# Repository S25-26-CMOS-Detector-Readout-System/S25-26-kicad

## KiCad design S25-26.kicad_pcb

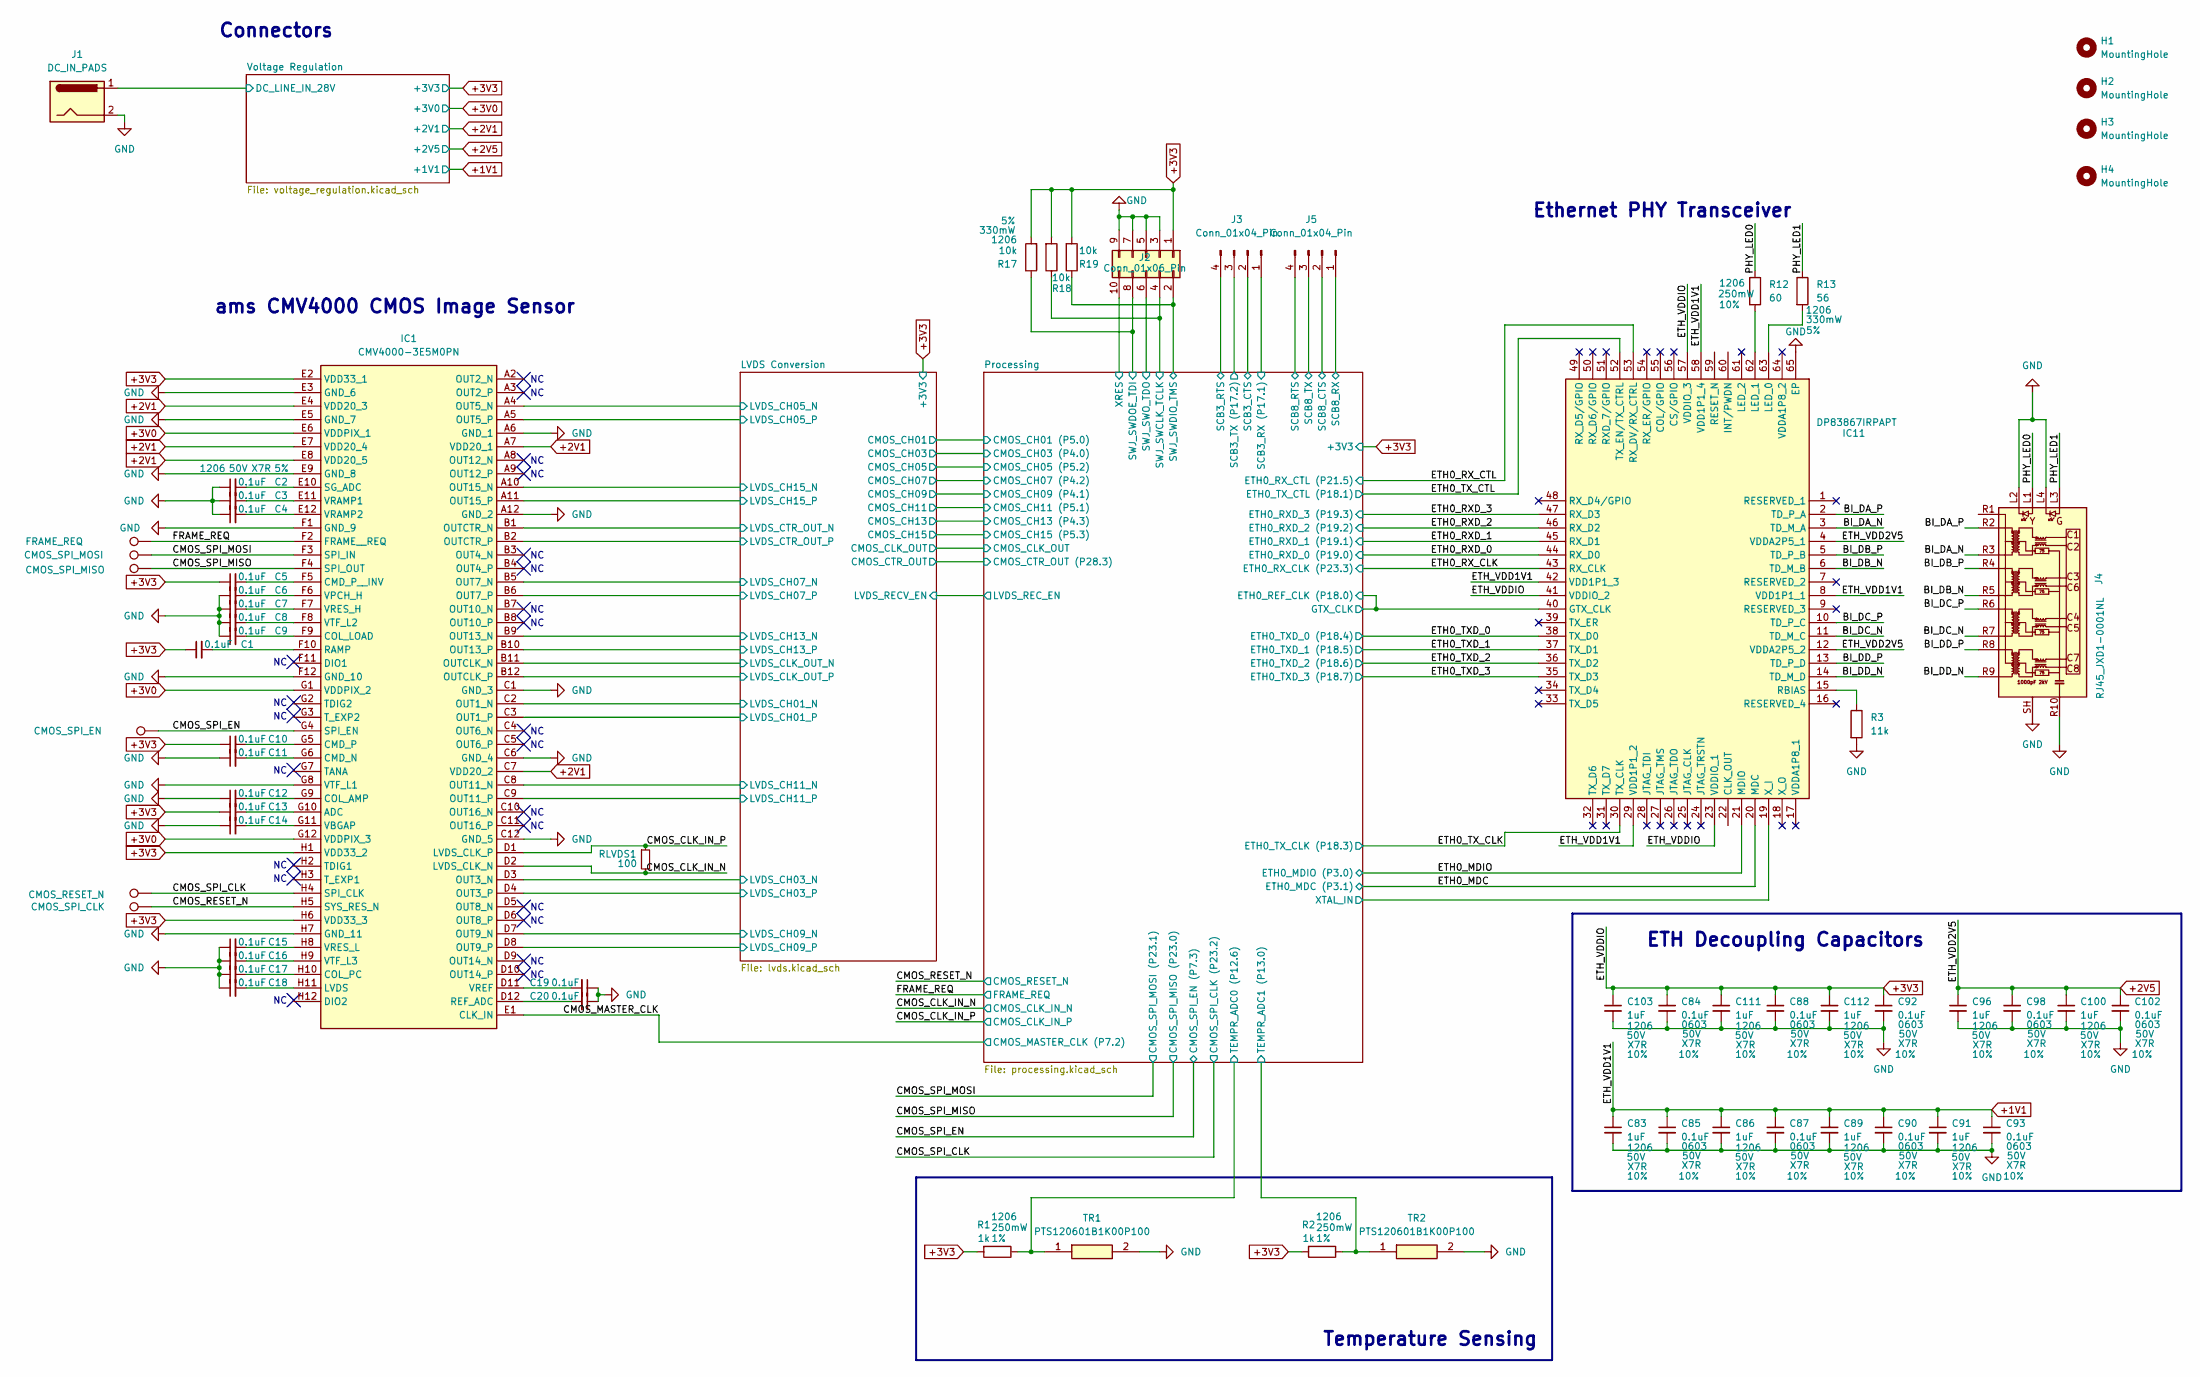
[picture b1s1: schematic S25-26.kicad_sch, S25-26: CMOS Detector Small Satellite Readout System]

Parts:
C1, C2, C3, C4, C5, C6, C7, C8, C9, C10, C11, C12, C13, C14, C15, C16, C17, C18, C19, C20: 0.1uF; C_1206_3216Metric; Voltage Rating 50V; Tolerance 5%; Mouser Part Number 581-12065C104J4Z2A
C83, C86, C89, C91, C96, C100, C103, C111, C112: 1uF; C_1206_3216Metric; Voltage Rating 50V; Tolerance 10%; Mouser Part Number 963-UMK316B7105KL-T
C84, C85, C87, C88, C90, C92, C93, C98, C102: 0.1uF; C_0603_1608Metric; Voltage Rating 50V; Tolerance 10%; Mouser Part Number 963-UMK107B7104KAHT
CMOS_RESET_N1: CMOS_RESET_N; TestPoint_Pad_2.0x2.0mm
CMOS_SCLK1: CMOS_SPI_CLK; TestPoint_Pad_2.0x2.0mm
CMOS_SPI_EN1: CMOS_SPI_EN; TestPoint_Pad_2.0x2.0mm
CMOS_SPI_MISO1: CMOS_SPI_MISO; TestPoint_Pad_2.0x2.0mm
CMOS_SPI_MOSI1: CMOS_SPI_MOSI; TestPoint_Pad_2.0x2.0mm
FRAME_REQ1: FRAME_REQ; TestPoint_Pad_2.0x2.0mm
H1, H2, H3, H4: MountingHole; MountingHole_2.7mm_Keepout
IC1: CMV4000-3E5M0PN; CMV40003E5M0PN_Socket; Manufacturer_Part_Number CMV4000-3E5M0PN
IC11: DP83867IRPAPT; QFP50P1200X1200X120-65N; Mouser Part Number 595-DP83867IRPAPT
J1: DC_IN_PADS; SolderWire-2sqmm_1x02_P7.8mm_D2mm_OD3.9mm
J2: Conn_01x06_Pin; PinHeader_2x05_P1.27mm_Vertical_SMD
J3, J5: Conn_01x04_Pin; PinHeader_1x04_P2.54mm_Vertical
J4: RJ45_JXD1-0001NL; Digikey Part Number 553-3266-ND
R1, R2: 1k; R_1206_3216Metric; Power Rating 250mW; Tolerance 1%; Mouser Part Number 71-RCA12061K00FKEA
R3: 11k; R_1206_3216Metric
R12: 60; R_1206_3216Metric; Power Rating 250mW; Tolerance 10%; Mouser Part Number 71-CRCW120660R0KNAIF
R13: 56; R_1206_3216Metric; Power Rating 330mW; Tolerance 5%; Mouser Part Number 667-ERJ-T08J560V
R17, R18, R19: 10k; R_1206_3216Metric; Power Rating 330mW; Tolerance 5%; Mouser Part Number 667-ERJ-T08J103V
RLVDS1: 100; R_0603_1608Metric; Power Rating 0.2W; Tolerance 1%; Mouser Part Number 667-ERJ-P03F1000V
TR1, TR2: PTS120601B1K00P100; RESC3016X65N; Manufacturer_Part_Number PTS120601B1K00P100; Mouser Part Number 594-PTS120601B1K00P

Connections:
+1V1: C83.1, C85.1, C86.1, C87.1, C89.1, C90.1, C91.1, C93.1, IC11.8 (VDD1P1_1), IC11.29 (VDD1P1_2), IC11.42 (VDD1P1_3), IC11.58 (VDD1P1_4); also elsewhere on the board
+2V1: IC1.A7 (VDD20_1), IC1.C7 (VDD20_2), IC1.E4 (VDD20_3), IC1.E7 (VDD20_4), IC1.E8 (VDD20_5); also elsewhere on the board
+2V5: C96.1, C98.1, C100.1, C102.1, IC11.4 (VDDA2P5_1), IC11.12 (VDDA2P5_2); also elsewhere on the board
+3V0: IC1.E6 (VDDPIX_1), IC1.G1 (VDDPIX_2), IC1.G12 (VDDPIX_3); also elsewhere on the board
+3V3: C1.1, C5.1, C10.1, C13.1, C84.1, C88.1, C92.1, C103.1, C111.1, C112.1, IC1.E2 (VDD33_1), IC1.H1 (VDD33_2), IC1.H6 (VDD33_3), IC11.23 (VDDIO_1), IC11.41 (VDDIO_2), IC11.57 (VDDIO_3), J2.1, R1.2, R2.2, R17.2, R18.2, R19.2; also elsewhere on the board
/BI_DA_N: IC11.3 (TD_M_A), J4.R3 (TD1-)
/BI_DA_P: IC11.2 (TD_P_A), J4.R2 (TD1+)
/BI_DB_N: IC11.6 (TD_M_B), J4.R5 (TD2-)
/BI_DB_P: IC11.5 (TD_P_B), J4.R4 (TD2+)
/BI_DC_N: IC11.11 (TD_M_C), J4.R7 (TD3-)
/BI_DC_P: IC11.10 (TD_P_C), J4.R6 (TD3+)
/BI_DD_N: IC11.14 (TD_M_D), J4.R9 (TD4-)
/BI_DD_P: IC11.13 (TD_P_D), J4.R8 (TD4+)
/CMOS_CLK_IN_N: IC1.D2 (LVDS_CLK_N), RLVDS1.2; also elsewhere on the board
/CMOS_CLK_IN_P: IC1.D1 (LVDS_CLK_P), RLVDS1.1; also elsewhere on the board
/CMOS_MASTER_CLK: IC1.E1 (CLK_IN); also elsewhere on the board
/CMOS_RESET_N: CMOS_SCLK1.1, IC1.H5 (SYS_RES_N); also elsewhere on the board
/CMOS_SPI_CLK: CMOS_RESET_N1.1, IC1.H4 (SPI_CLK); also elsewhere on the board
/CMOS_SPI_EN: CMOS_SPI_EN1.1, IC1.G4 (SPI_EN); also elsewhere on the board
/CMOS_SPI_MISO: CMOS_SPI_MISO1.1, IC1.F4 (SPI_OUT); also elsewhere on the board
/CMOS_SPI_MOSI: CMOS_SPI_MOSI1.1, IC1.F3 (SPI_IN); also elsewhere on the board
/ETH0_MDC: IC11.20 (MDC); also elsewhere on the board
/ETH0_MDIO: IC11.21 (MDIO); also elsewhere on the board
/ETH0_RXD_0: IC11.44 (RX_D0); also elsewhere on the board
/ETH0_RXD_1: IC11.45 (RX_D1); also elsewhere on the board
/ETH0_RXD_2: IC11.46 (RX_D2); also elsewhere on the board
/ETH0_RXD_3: IC11.47 (RX_D3); also elsewhere on the board
/ETH0_RX_CLK: IC11.43 (RX_CLK); also elsewhere on the board
/ETH0_RX_CTL: IC11.53 (RX_DV/RX_CTRL); also elsewhere on the board
/ETH0_TXD_0: IC11.38 (TX_D0); also elsewhere on the board
/ETH0_TXD_1: IC11.37 (TX_D1); also elsewhere on the board
/ETH0_TXD_2: IC11.36 (TX_D2); also elsewhere on the board
/ETH0_TXD_3: IC11.35 (TX_D3); also elsewhere on the board
/ETH0_TX_CLK: IC11.30 (TX_CLK); also elsewhere on the board
/ETH0_TX_CTL: IC11.52 (TX_EN/TX_CTRL); also elsewhere on the board
/FRAME_REQ: FRAME_REQ1.1, IC1.F2 (FRAME__REQ); also elsewhere on the board
/LVDS Conversion/LVDS_CH01_N: IC1.C2 (OUT1_N); also elsewhere on the board
/LVDS Conversion/LVDS_CH01_P: IC1.C3 (OUT1_P); also elsewhere on the board
/LVDS Conversion/LVDS_CH03_N: IC1.D3 (OUT3_N); also elsewhere on the board
/LVDS Conversion/LVDS_CH03_P: IC1.D4 (OUT3_P); also elsewhere on the board
/LVDS Conversion/LVDS_CH05_N: IC1.A4 (OUT5_N); also elsewhere on the board
/LVDS Conversion/LVDS_CH05_P: IC1.A5 (OUT5_P); also elsewhere on the board
/LVDS Conversion/LVDS_CH07_N: IC1.B5 (OUT7_N); also elsewhere on the board
/LVDS Conversion/LVDS_CH07_P: IC1.B6 (OUT7_P); also elsewhere on the board
/LVDS Conversion/LVDS_CH09_N: IC1.D7 (OUT9_N); also elsewhere on the board
/LVDS Conversion/LVDS_CH09_P: IC1.D8 (OUT9_P); also elsewhere on the board
/LVDS Conversion/LVDS_CH11_N: IC1.C8 (OUT11_N); also elsewhere on the board
/LVDS Conversion/LVDS_CH11_P: IC1.C9 (OUT11_P); also elsewhere on the board
/LVDS Conversion/LVDS_CH13_N: IC1.B9 (OUT13_N); also elsewhere on the board
/LVDS Conversion/LVDS_CH13_P: IC1.B10 (OUT13_P); also elsewhere on the board
/LVDS Conversion/LVDS_CH15_N: IC1.A10 (OUT15_N); also elsewhere on the board
/LVDS Conversion/LVDS_CH15_P: IC1.A11 (OUT15_P); also elsewhere on the board
/LVDS Conversion/LVDS_CLK_OUT_N: IC1.B11 (OUTCLK_N); also elsewhere on the board
/LVDS Conversion/LVDS_CLK_OUT_P: IC1.B12 (OUTCLK_P); also elsewhere on the board
/LVDS Conversion/LVDS_CTR_OUT_N: IC1.B1 (OUTCTR_N); also elsewhere on the board
/LVDS Conversion/LVDS_CTR_OUT_P: IC1.B2 (OUTCTR_P); also elsewhere on the board
/PHY_LED0: J4.L1, R12.1
/PHY_LED1: J4.L3, R13.1
/Processing/ETH0_REF_CLK (P18.0): IC11.40 (GTX_CLK); also elsewhere on the board
/Processing/SCB3_CTS: J3.2; also elsewhere on the board
/Processing/SCB3_RTS: J3.4; also elsewhere on the board
/Processing/SCB3_RX (P17.1): J3.1; also elsewhere on the board
/Processing/SCB3_TX (P17.2): J3.3; also elsewhere on the board
/Processing/SCB8_CTS: J5.2; also elsewhere on the board
/Processing/SCB8_RTS: J5.4; also elsewhere on the board
/Processing/SCB8_RX: J5.1; also elsewhere on the board
/Processing/SCB8_TX: J5.3; also elsewhere on the board
/Processing/SWJ_SWCLK_TCLK: J2.4, R18.1; also elsewhere on the board
/Processing/SWJ_SWDIO_TMS: J2.2, R19.1; also elsewhere on the board
/Processing/SWJ_SWDOE_TDI: J2.8, R17.1; also elsewhere on the board
/Processing/SWJ_SWO_TDO: J2.6; also elsewhere on the board
/Processing/TEMPR_ADC0 (P12.6): R1.1, TR1.1; also elsewhere on the board
/Processing/TEMPR_ADC1 (P13.0): R2.1, TR2.1; also elsewhere on the board
/Processing/XRES: J2.10; also elsewhere on the board
/Processing/XTAL_IN: IC11.19 (X_I); also elsewhere on the board
/Voltage Regulation/DC_LINE_IN_28V: J1.1; also elsewhere on the board
GND: C2.1, C3.1, C4.1, C6.1, C7.1, C8.1, C9.1, C11.1, C12.1, C14.1, C15.1, C16.1, C17.1, C18.1, C19.1, C20.1, C83.2, C84.2, C85.2, C86.2, C87.2, C88.2, C89.2, C90.2, C91.2, C92.2, C93.2, C96.2, C98.2, C100.2, C102.2, C103.2, C111.2, C112.2, IC1.A6 (GND_1), IC1.A12 (GND_2), IC1.C1 (GND_3), IC1.C6 (GND_4), IC1.C12 (GND_5), IC1.E3 (GND_6), IC1.E5 (GND_7), IC1.E9 (GND_8), IC1.F1 (GND_9), IC1.F12 (GND_10), IC1.G8 (VTF_L1), IC1.H7 (GND_11), IC11.65 (EP), J1.2, J2.3, J2.5, J2.7, J2.9, J4.L2, J4.L4, J4.R10 (GND), J4.SH, R3.2, TR1.2, TR2.2; also elsewhere on the board
unnamed: C13.2, IC1.G10 (ADC)
unnamed: C11.2, IC1.G6 (CMD_N)
unnamed: C10.2, IC1.G5 (CMD_P)
unnamed: C5.2, IC1.F5 (CMD_P__INV)
unnamed: C12.2, IC1.G9 (COL_AMP)
unnamed: C9.2, IC1.F9 (COL_LOAD)
unnamed: C17.2, IC1.H10 (COL_PC)
unnamed: C18.2, IC1.H11 (LVDS)
unnamed: C1.2, IC1.F10 (RAMP)
unnamed: C20.2, IC1.D12 (REF_ADC)
unnamed: C2.2, IC1.E10 (SG_ADC)
unnamed: C14.2, IC1.G11 (VBGAP)
unnamed: C6.2, IC1.F6 (VPCH_H)
unnamed: C3.2, IC1.E11 (VRAMP1)
unnamed: C4.2, IC1.E12 (VRAMP2)
unnamed: C19.2, IC1.D11 (VREF)
unnamed: C7.2, IC1.F7 (VRES_H)
unnamed: C15.2, IC1.H8 (VRES_L)
unnamed: C8.2, IC1.F8 (VTF_L2)
unnamed: C16.2, IC1.H9 (VTF_L3)
unnamed: IC11.63 (LED_0), R13.2
unnamed: IC11.62 (LED_1), R12.2
unnamed: IC11.15 (RBIAS), R3.1

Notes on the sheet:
ams CMV4000 CMOS Image Sensor
Ethernet PHY Transceiver
Connectors
ETH Decoupling Capacitors
Temperature Sensing

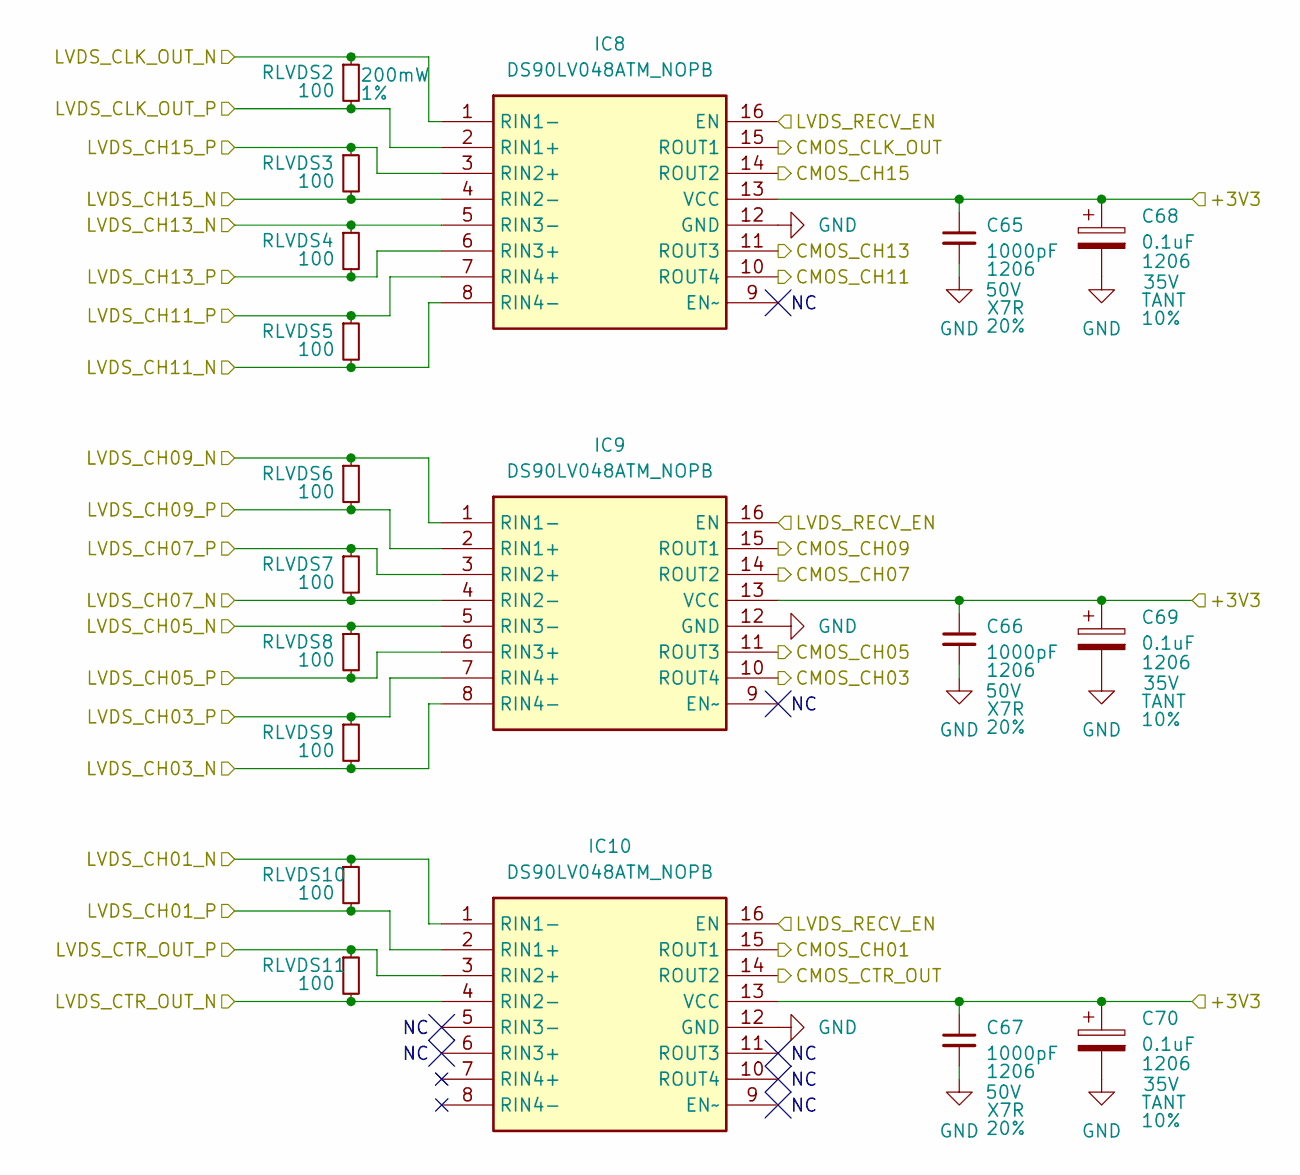
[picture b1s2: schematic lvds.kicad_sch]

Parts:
C65, C66, C67: 1000pF; C_1206_3216Metric; Voltage Rating 50V; Tolerance 20%; Mouser Part Number 80-C1206C102M5RACTM
C68, C69, C70: 0.1uF; C_1206_3216Metric; Voltage Rating 35V; Tolerance 10%; Mouser Part Number 581-TAJA104K035SNJ
IC8, IC9, IC10: DS90LV048ATM_NOPB; SOIC127P600X175-16N; Manufacturer_Part_Number DS90LV048ATM/NOPB; Mouser Part Number :926-DS90LV048ATMNOPB
RLVDS2: 100; R_0603_1608Metric; Power Rating 200mW; Tolerance 1%; Mouser Part Number 667-ERJ-P03F1000V
RLVDS3, RLVDS4, RLVDS5, RLVDS6, RLVDS7, RLVDS8, RLVDS9, RLVDS10, RLVDS11: 100; R_0603_1608Metric; Power Rating 0.2W; Tolerance 1%; Mouser Part Number 667-ERJ-P03F1000V

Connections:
+3V3: C65.1, C66.1, C67.1, C68.1, C69.1, C70.1, IC8.13 (VCC), IC9.13 (VCC), IC10.13 (VCC); also elsewhere on the board
/LVDS Conversion/CMOS_CH01: IC10.15 (ROUT1); also elsewhere on the board
/LVDS Conversion/CMOS_CH03: IC9.10 (ROUT4); also elsewhere on the board
/LVDS Conversion/CMOS_CH05: IC9.11 (ROUT3); also elsewhere on the board
/LVDS Conversion/CMOS_CH07: IC9.14 (ROUT2); also elsewhere on the board
/LVDS Conversion/CMOS_CH09: IC9.15 (ROUT1); also elsewhere on the board
/LVDS Conversion/CMOS_CH11: IC8.10 (ROUT4); also elsewhere on the board
/LVDS Conversion/CMOS_CH13: IC8.11 (ROUT3); also elsewhere on the board
/LVDS Conversion/CMOS_CH15: IC8.14 (ROUT2); also elsewhere on the board
/LVDS Conversion/CMOS_CLK_OUT: IC8.15 (ROUT1); also elsewhere on the board
/LVDS Conversion/CMOS_CTR_OUT: IC10.14 (ROUT2); also elsewhere on the board
/LVDS Conversion/LVDS_CH01_N: IC10.1 (RIN1-), RLVDS10.1; also elsewhere on the board
/LVDS Conversion/LVDS_CH01_P: IC10.2 (RIN1+), RLVDS10.2; also elsewhere on the board
/LVDS Conversion/LVDS_CH03_N: IC9.8 (RIN4-), RLVDS9.2; also elsewhere on the board
/LVDS Conversion/LVDS_CH03_P: IC9.7 (RIN4+), RLVDS9.1; also elsewhere on the board
/LVDS Conversion/LVDS_CH05_N: IC9.5 (RIN3-), RLVDS8.1; also elsewhere on the board
/LVDS Conversion/LVDS_CH05_P: IC9.6 (RIN3+), RLVDS8.2; also elsewhere on the board
/LVDS Conversion/LVDS_CH07_N: IC9.4 (RIN2-), RLVDS7.2; also elsewhere on the board
/LVDS Conversion/LVDS_CH07_P: IC9.3 (RIN2+), RLVDS7.1; also elsewhere on the board
/LVDS Conversion/LVDS_CH09_N: IC9.1 (RIN1-), RLVDS6.1; also elsewhere on the board
/LVDS Conversion/LVDS_CH09_P: IC9.2 (RIN1+), RLVDS6.2; also elsewhere on the board
/LVDS Conversion/LVDS_CH11_N: IC8.8 (RIN4-), RLVDS5.2; also elsewhere on the board
/LVDS Conversion/LVDS_CH11_P: IC8.7 (RIN4+), RLVDS5.1; also elsewhere on the board
/LVDS Conversion/LVDS_CH13_N: IC8.5 (RIN3-), RLVDS4.1; also elsewhere on the board
/LVDS Conversion/LVDS_CH13_P: IC8.6 (RIN3+), RLVDS4.2; also elsewhere on the board
/LVDS Conversion/LVDS_CH15_N: IC8.4 (RIN2-), RLVDS3.2; also elsewhere on the board
/LVDS Conversion/LVDS_CH15_P: IC8.3 (RIN2+), RLVDS3.1; also elsewhere on the board
/LVDS Conversion/LVDS_CLK_OUT_N: IC8.1 (RIN1-), RLVDS2.1; also elsewhere on the board
/LVDS Conversion/LVDS_CLK_OUT_P: IC8.2 (RIN1+), RLVDS2.2; also elsewhere on the board
/LVDS Conversion/LVDS_CTR_OUT_N: IC10.4 (RIN2-), RLVDS11.2; also elsewhere on the board
/LVDS Conversion/LVDS_CTR_OUT_P: IC10.3 (RIN2+), RLVDS11.1; also elsewhere on the board
/LVDS Conversion/LVDS_RECV_EN: IC8.16 (EN), IC9.16 (EN), IC10.16 (EN); also elsewhere on the board
GND: C65.2, C66.2, C67.2, C68.2, C69.2, C70.2, IC8.12 (GND), IC9.12 (GND), IC10.12 (GND); also elsewhere on the board

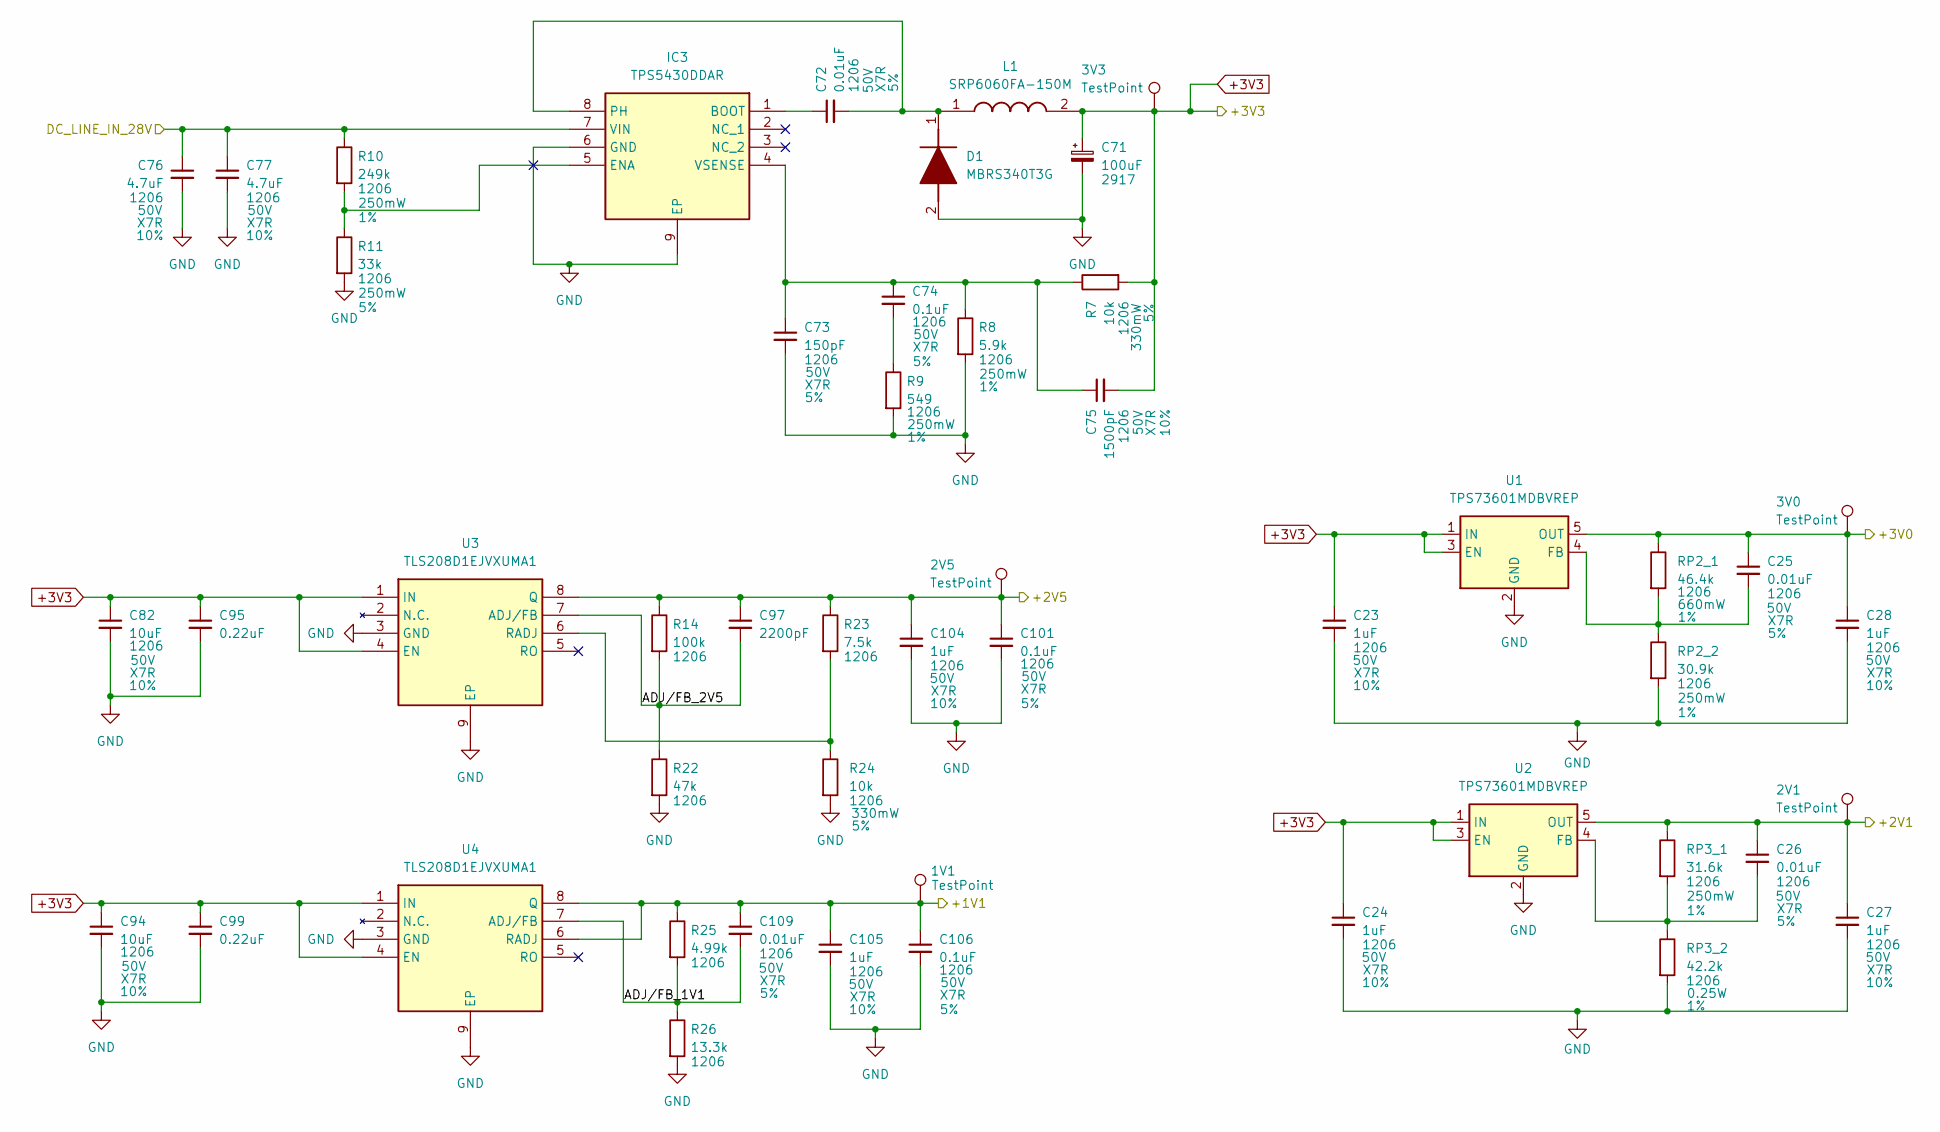
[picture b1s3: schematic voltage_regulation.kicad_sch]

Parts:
1V1, 2V1, 2V5, 3V0, 3V3: TestPoint; TestPoint_Pad_D1.0mm
C23, C24, C27, C28, C104, C105: 1uF; C_1206_3216Metric; Voltage Rating 50V; Tolerance 10%; Mouser Part Number 963-UMK316B7105KL-T
C25, C26, C72, C109: 0.01uF; C_1206_3216Metric; Voltage Rating 50V; Tolerance 5%; Mouser Part Number 581-12065C103J4T4A
C71: 100uF; CP_EIA-7343-15_Kemet-W; Mouser Part Number 74-293D107X9010D2TE3
C73: 150pF; C_1206_3216Metric; Voltage Rating 50V; Tolerance 5%; Mouser Part Number 80-C1206C151J5RACTU
C74, C101, C106: 0.1uF; C_1206_3216Metric; Voltage Rating 50V; Tolerance 5%; Mouser Part Number 581-12065C104J4Z2A
C75: 1500pF; C_1206_3216Metric; Voltage Rating 50V; Tolerance 10%; Mouser Part Number 77-VJ1206Y152KXAAC
C76, C77: 4.7uF; C_1206_3216Metric; Voltage Rating 50V; Tolerance 10%; Mouser Part Number 581-KGM31AR71H475KU
C82, C94: 10uF; C_1206_3216Metric; Voltage Rating 50V; Tolerance 10%; Mouser Part Number 187-CL31B106KBK6PJE
C95, C99: 0.22uF; C_1206_3216Metric
C97: 2200pF; C_1206_3216Metric
D1: MBRS340T3G; DIOM8059X261N; Mouser Part Number 863-MBRS340T3G
IC3: TPS5430DDAR; SOIC127P600X170-9N; Mouser Part Number 595-TPS5430DDAR
L1: SRP6060FA-150M; SRP6060FA150M; Mouser Part Number 652-SRP6060FA-150M
R7, R24: 10k; R_1206_3216Metric; Power Rating 330mW; Tolerance 5%; Mouser Part Number 667-ERJ-T08J103V
R8: 5.9k; R_1206_3216Metric; Power Rating 250mW; Tolerance 1%; Mouser Part Number 71-CRCW1206-5.9K-E3
R9: 549; R_1206_3216Metric; Power Rating 250mW; Tolerance 1%; Mouser Part Number 71-CRCW1206-549-E3
R10: 249k; R_1206_3216Metric; Power Rating 250mW; Tolerance 1%; Mouser Part Number 71-RCV1206249KFKEA
R11: 33k; R_1206_3216Metric; Power Rating 250mW; Tolerance 5%; Mouser Part Number 755-KTR18EZPJ333
R14: 100k; R_1206_3216Metric
R22: 47k; R_1206_3216Metric
R23: 7.5k; R_1206_3216Metric
R25: 4.99k; R_1206_3216Metric
R26: 13.3k; R_1206_3216Metric
RP2_1: 46.4k; R_1206_3216Metric; Power Rating 660mW; Tolerance 1%; Mouser Part Number 667-ERJ-P08F4642V
RP2_2: 30.9k; R_1206_3216Metric; Power Rating 250mW; Tolerance 1%; Mouser Part Number 652-CR1206FX-3092ELF
RP3_1: 31.6k; R_1206_3216Metric; Power Rating 250mW; Tolerance 1%; Mouser Part Number 71-CRCW120631K6FKEAC
RP3_2: 42.2k; R_1206_3216Metric; Power Rating 0.25W; Tolerance 1%; Mouser Part Number 71-CRCW1206-42.2K
U1, U2: TPS73601MDBVREP; SOT-23-5; Mouser Part Number 595-TPS73601MDBVREP
U3, U4: TLS208D1EJVXUMA1; SOIC127P600X170-9N; Mouser Part Number 726-TLS208D1EJVXUMA1

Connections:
+1V1: 1V1.1, C105.1, C106.1, C109.1, R25.1, U4.6 (RADJ), U4.8 (Q); also elsewhere on the board
+2V1: 2V1.1, C26.1, C27.1, RP3_1.1, U2.5 (OUT); also elsewhere on the board
+2V5: 2V5.1, C97.1, C101.1, C104.1, R14.1, R23.1, U3.8 (Q); also elsewhere on the board
+3V0: 3V0.1, C25.1, C28.1, RP2_1.1, U1.5 (OUT); also elsewhere on the board
+3V3: 3V3.1, C23.1, C24.1, C71.1, C75.2, C82.1, C94.1, C95.1, C99.1, L1.2, R7.2, U1.1 (IN), U1.3 (EN), U2.1 (IN), U2.3 (EN), U3.1 (IN), U3.4 (EN), U4.1 (IN), U4.4 (EN); also elsewhere on the board
/Voltage Regulation/ADJ/FB_1V1: C109.2, R25.2, R26.1, U4.7 (ADJ/FB)
/Voltage Regulation/ADJ/FB_2V5: C97.2, R14.2, R22.1, U3.7 (ADJ/FB)
/Voltage Regulation/DC_LINE_IN_28V: C76.1, C77.1, IC3.7 (VIN), R10.1; also elsewhere on the board
GND: C23.2, C24.2, C27.2, C28.2, C71.2, C73.2, C76.2, C77.2, C82.2, C94.2, C95.2, C99.2, C101.2, C104.2, C105.2, C106.2, D1.2 (A), IC3.6 (GND), IC3.9 (EP), R8.2, R9.2, R11.2, R22.2, R24.2, R26.2, RP2_2.2, RP3_2.2, U1.2 (GND), U2.2 (GND), U3.3 (GND), U3.9 (EP), U4.3 (GND), U4.9 (EP); also elsewhere on the board
unnamed: C74.2, R9.1
unnamed: C72.2, D1.1 (K), IC3.8 (PH), L1.1
unnamed: C72.1, IC3.1 (BOOT)
unnamed: IC3.5 (ENA), R10.2, R11.1
unnamed: C73.1, C74.1, C75.1, IC3.4 (VSENSE), R7.1, R8.1
unnamed: C25.2, RP2_1.2, RP2_2.1, U1.4 (FB)
unnamed: C26.2, RP3_1.2, RP3_2.1, U2.4 (FB)
unnamed: R23.2, R24.1, U3.6 (RADJ)
